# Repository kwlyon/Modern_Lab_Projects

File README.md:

# Modern Lab Projects

This repository collects four laboratory data-acquisition projects. The active
differential Arduino firmware is maintained in `Frank_Herz` and also used by
`SerialPlotter_V3`.

| Project | Contents |
| --- | --- |
| [Frank_Herz](Frank_Herz/README.md) | Franck–Hertz acquisition software and differential Arduino shield firmware |
| [SerialPlotter](SerialPlotter/README.md) | Original serial plotter and earlier shield designs |
| [SerialPlotter_V2](SerialPlotter_V2/README.md) | Two-channel recorder with the older single-ended Arduino sketch |
| [SerialPlotter_V3](SerialPlotter_V3/README.md) | General recorder, Eagle design for the current differential shield, and Arduino averaging |

The three original projects were imported with unsquashed Git subtree merges.
Their commits remain in this repository's history. Frank_Herz release tags are retained
under `Frank_Herz/v...` names so they remain distinct from future tags for other
projects.

See each project's README for build, calibration, and hardware instructions.
For the current differential shield, use the
[Frank–Herz sketch](Frank_Herz/arduino/Frank_Herz_DAQ/Frank_Herz_DAQ.ino)
with either the Frank–Herz app or Serial Plotter V3.
Frank–Hertz Windows downloads and firmware attachments are available on the
[releases page](https://github.com/kwlyon/Modern_Lab_Projects/releases).

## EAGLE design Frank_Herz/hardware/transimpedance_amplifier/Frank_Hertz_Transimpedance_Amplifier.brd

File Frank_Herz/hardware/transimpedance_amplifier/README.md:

# Frank–Hertz transimpedance amplifier

This is the separate current-to-voltage amplifier for the Frank–Hertz
experiment, **not** the Arduino acquisition shield. The original Eagle project
was `Box/eShop/Eagle/Eagle Projects/Modern Lab/Frank_Hertz`.

- [`Frank_Hertz_Transimpedance_Amplifier.sch`](Frank_Hertz_Transimpedance_Amplifier.sch) — Eagle schematic.
- [`Frank_Hertz_Transimpedance_Amplifier.brd`](Frank_Hertz_Transimpedance_Amplifier.brd) — Eagle board.
The Eagle schematic and board were copied byte for byte; only their filenames
changed. Fabrication outputs remain in the original Eagle project. Run ERC/DRC
and generate fresh Gerbers from this board before ordering boards.

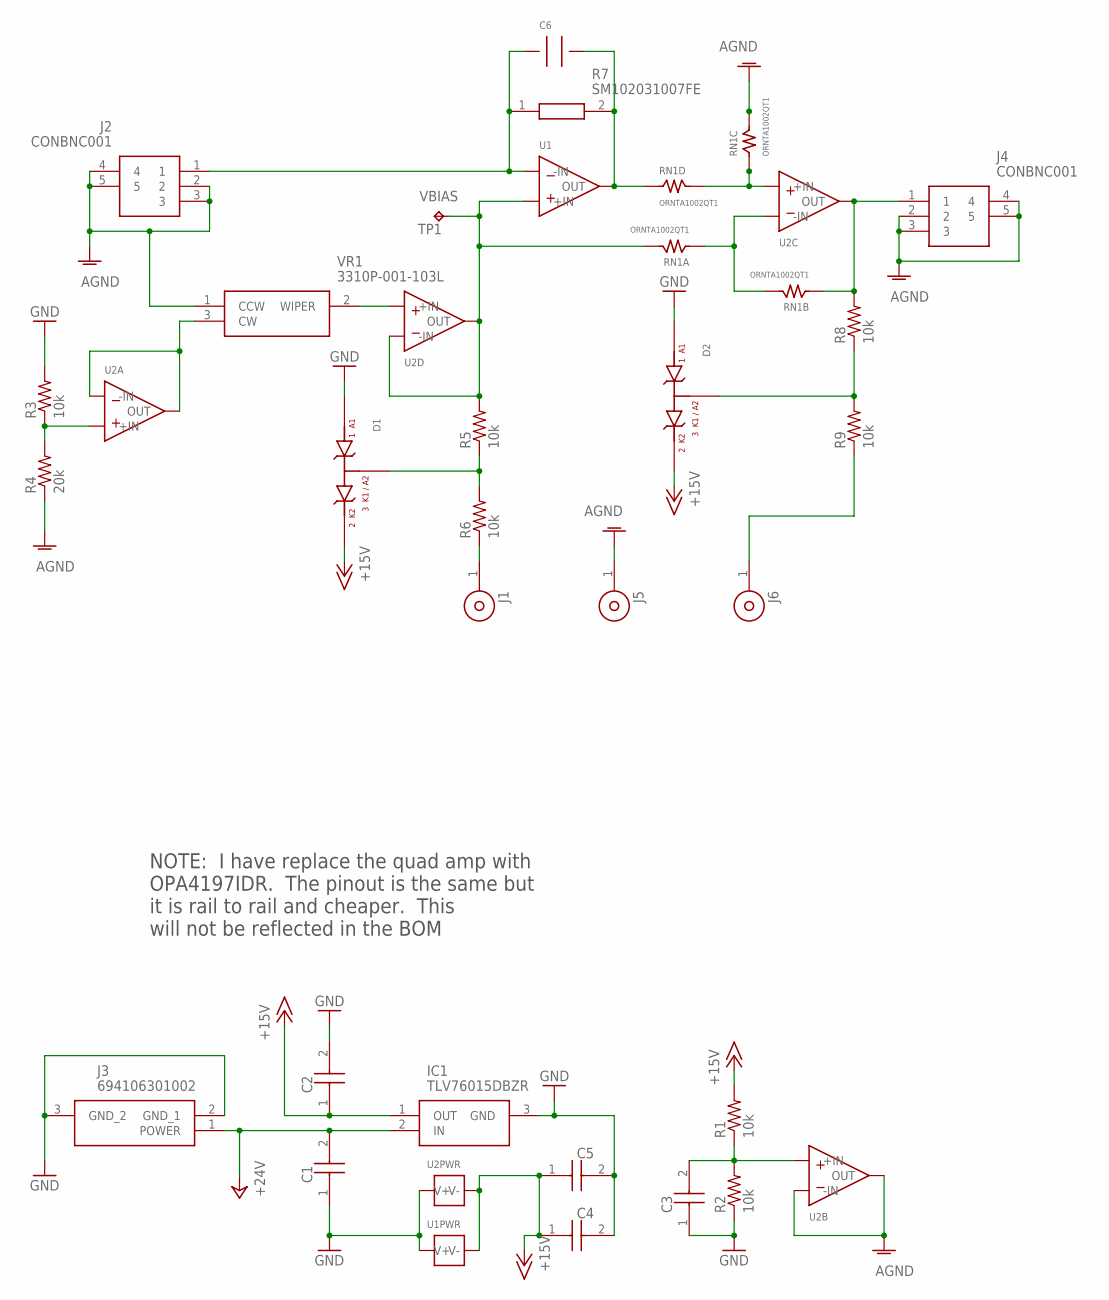
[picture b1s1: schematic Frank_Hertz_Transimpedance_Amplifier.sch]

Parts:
C1, C2, C3: 1uF; CAPC2012X140N
C4, C5: CC0603KRX7R8BB104; CAPC1608X90N
C6: C315C109D2G5TA_10.16MM; C315_BENT_10.16MM
D1, D2: BAS70_04_SOT23COMMERCIAL_REELNXP; SOT23-3_NEXPERIA
IC1: TLV76015DBZR; SOT95P237X112-3N
J1, J5, J6: CINCH_108-0904-001; CINCH_108-0904-001_BODGE
J2, J4: CONBNC001
J3: 694106301002
R1, R2, R3, R5, R6, R8, R9: 10k; R0805
R4: 20k; R0805
R7: SM102031007FE
RN1: ORNTA1002QT1; SOIC8_MS012_AA_1.27MM
TP1: TPB1,27; B1,27
U1: LMC6081IN/NOPB; PDIP-8_300MIL
U2: OPA4227UA_SOIC14; SOIC-14_D
VR1: 3310P-001-103L; 3310P001103L

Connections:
+15V: C2.1, C4.1, C5.1, D1.2 (K2), D2.2 (K2), IC1.1 (OUT), R1.2, U1.7 (V+), U2.4 (V+)
+24V: C1.2, IC1.2 (IN), J3.1 (POWER)
AGND: J2.2, J2.3, J2.4, J2.5, J4.2, J4.3, J4.4, J4.5, J5.1, R4.1, RN1.6 (2), U2.6 (-IN), U2.7 (OUT), VR1.1 (CCW)
GND: C1.1, C2.2, C3.1, C4.2, C5.2, D1.1 (A1), D2.1 (A1), IC1.3 (GND), J3.2 (GND_1), J3.3 (GND_2), R2.1, R3.2, U1.4 (V-), U2.11 (V-)
unnamed: U2.12 (+IN), VR1.2 (WIPER)
unnamed: C3.2, R1.1, R2.2, U2.5 (+IN)
unnamed: J6.1, R9.1
unnamed: R3.1, R4.2, U2.3 (+IN)
unnamed: U2.1 (OUT), U2.2 (-IN), VR1.3 (CW)
unnamed: C6.1, J2.1, R7.1, U1.2 (-IN)
unnamed: RN1.1, RN1.7 (2), U2.9 (-IN)
unnamed: C6.2, R7.2, RN1.4 (1), U1.6 (OUT)
unnamed: RN1.3 (1), RN1.5 (2), U2.10 (+IN)
unnamed: J4.1, R8.2, RN1.2 (1), U2.8 (OUT)
unnamed: D1.3 (K1_A2), R5.1, R6.2
unnamed: J1.1, R6.1
unnamed: D2.3 (K1_A2), R8.1, R9.2
VBIAS: R5.2, RN1.8 (2), TP1.TP, U1.3 (+IN), U2.13 (-IN), U2.14 (OUT)

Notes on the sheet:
NOTE: I have replace the quad amp with OPA4197IDR. The pinout is the same but it is rail to rail and cheaper. This will not be reflected in the BOM

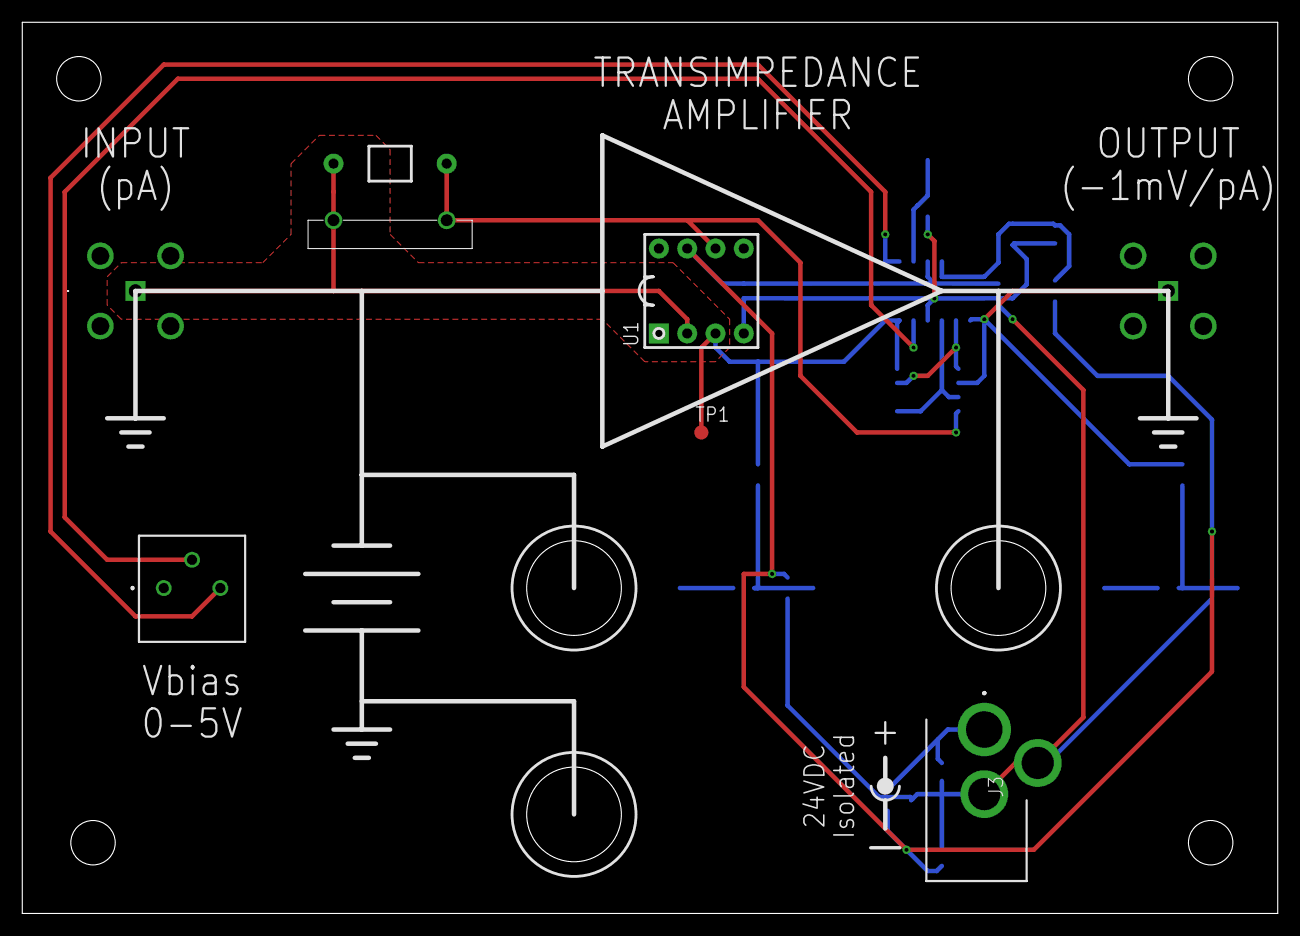
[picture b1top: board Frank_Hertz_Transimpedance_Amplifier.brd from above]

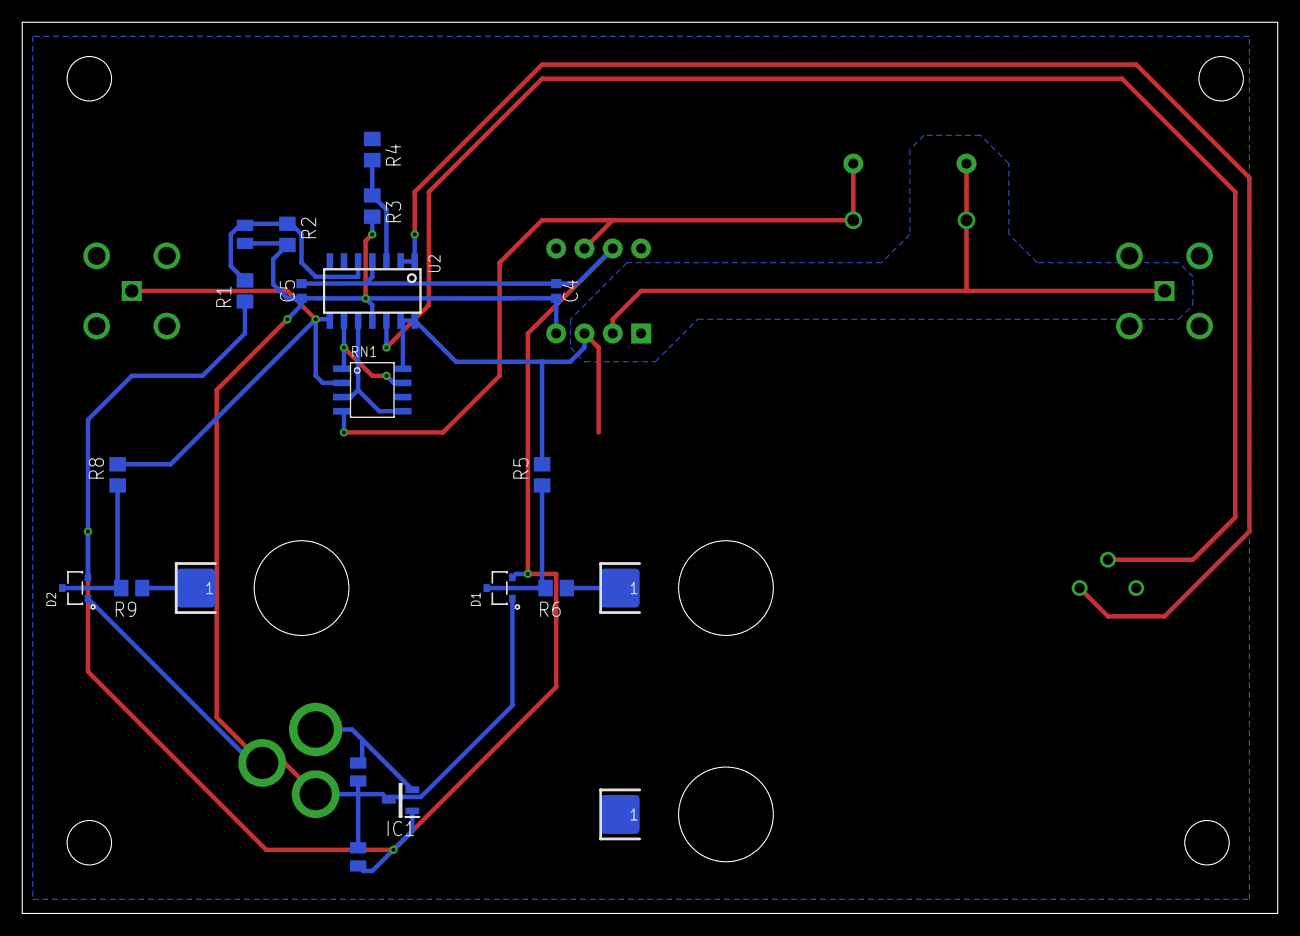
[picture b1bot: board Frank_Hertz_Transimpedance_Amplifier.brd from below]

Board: 2 copper layers, 112.7 x 80.0 mm, 29 parts (18 on the bottom side), 18 nets.

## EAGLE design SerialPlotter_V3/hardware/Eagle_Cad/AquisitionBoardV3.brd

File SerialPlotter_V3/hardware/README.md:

# Current differential Arduino shield

[`Eagle_Cad/AquisitionBoardV3.sch`](Eagle_Cad/AquisitionBoardV3.sch) and
[`Eagle_Cad/AquisitionBoardV3.brd`](Eagle_Cad/AquisitionBoardV3.brd) are the
schematic and board for the current Modern Lab shield. They were copied from
the Modern Lab **Atomic and Molecular / Arduino Shield for Aquisition** Eagle
project. Their original Eagle filenames are retained.

[`Eagle_Cad/AquisitionBoardV3_Gerbers.zip`](Eagle_Cad/AquisitionBoardV3_Gerbers.zip)
contains the corresponding fabrication outputs. The archive was copied from
that project's `CAMOutputs/GerberFiles/AquisitionV3.zip` and renamed to match
the board and schematic. Its Gerber job identifies project `AquisitionBoardV3`
and includes copper, solder mask, solder paste, silkscreen, board profile, and
drill files. The original archive remains in the Eagle project.

[`Mouser_BOM_Differential_Arduino_Shield_One_Board.xlsx`](Mouser_BOM_Differential_Arduino_Shield_One_Board.xlsx)
is a one-board parts list based on this board's placed elements. It uses the
columns from the supplied Mouser template, with added designators, footprints,
selection notes, and product links. The 21 order lines cover 56 individual
parts or kits, including one Arduino R3 stacking-header kit. The Arduino and
fabricated PCB are not included. SJ1/SJ2 are solder jumper pads and TP1 is a
bare test pad, so they do not need purchased parts. The optional AGND/BGND
header posts are listed. Check the J2 DE-9 connector's physical fit against
the Eagle footprint before ordering; its manufacturer part number is a
candidate selection. Prices and availability should be refreshed in Mouser.

The board's top silkscreen has circled **A** and **B** labels. Unlike the older
files with the same names in
[`../../SerialPlotter/Arduino Shield for Aquisition/Eagle_Cad/`](../../SerialPlotter/Arduino%20Shield%20for%20Aquisition/Eagle_Cad/),
this board has no 15-turn Bourns 3006P trimmer. The older Eagle designs stay
there for reference. Eagle may retain unused library definitions in the files;
the placed board elements are the check for whether a part is fitted.

The schematic routes Channel A through J1 and the 909 kΩ / 101 kΩ divider to
ADS1115 AIN0−AIN1. Channel B uses J3 and the corresponding divider on
AIN2−AIN3. A 10 kΩ resistor pulls the ADC's ADDR pin to +5 V for I2C address
`0x49` when solder jumper SJ1 is open. This matches the maintained
[`Frank_Herz_DAQ.ino`](../../Frank_Herz/arduino/Frank_Herz_DAQ/Frank_Herz_DAQ.ino)
firmware used by both Franck–Hertz and Serial Plotter V3.

The files were checked for matching placed parts and schematic pin connections.
Physical electrical verification and an Eagle ERC/DRC run are still needed
before fabrication or hardware changes.

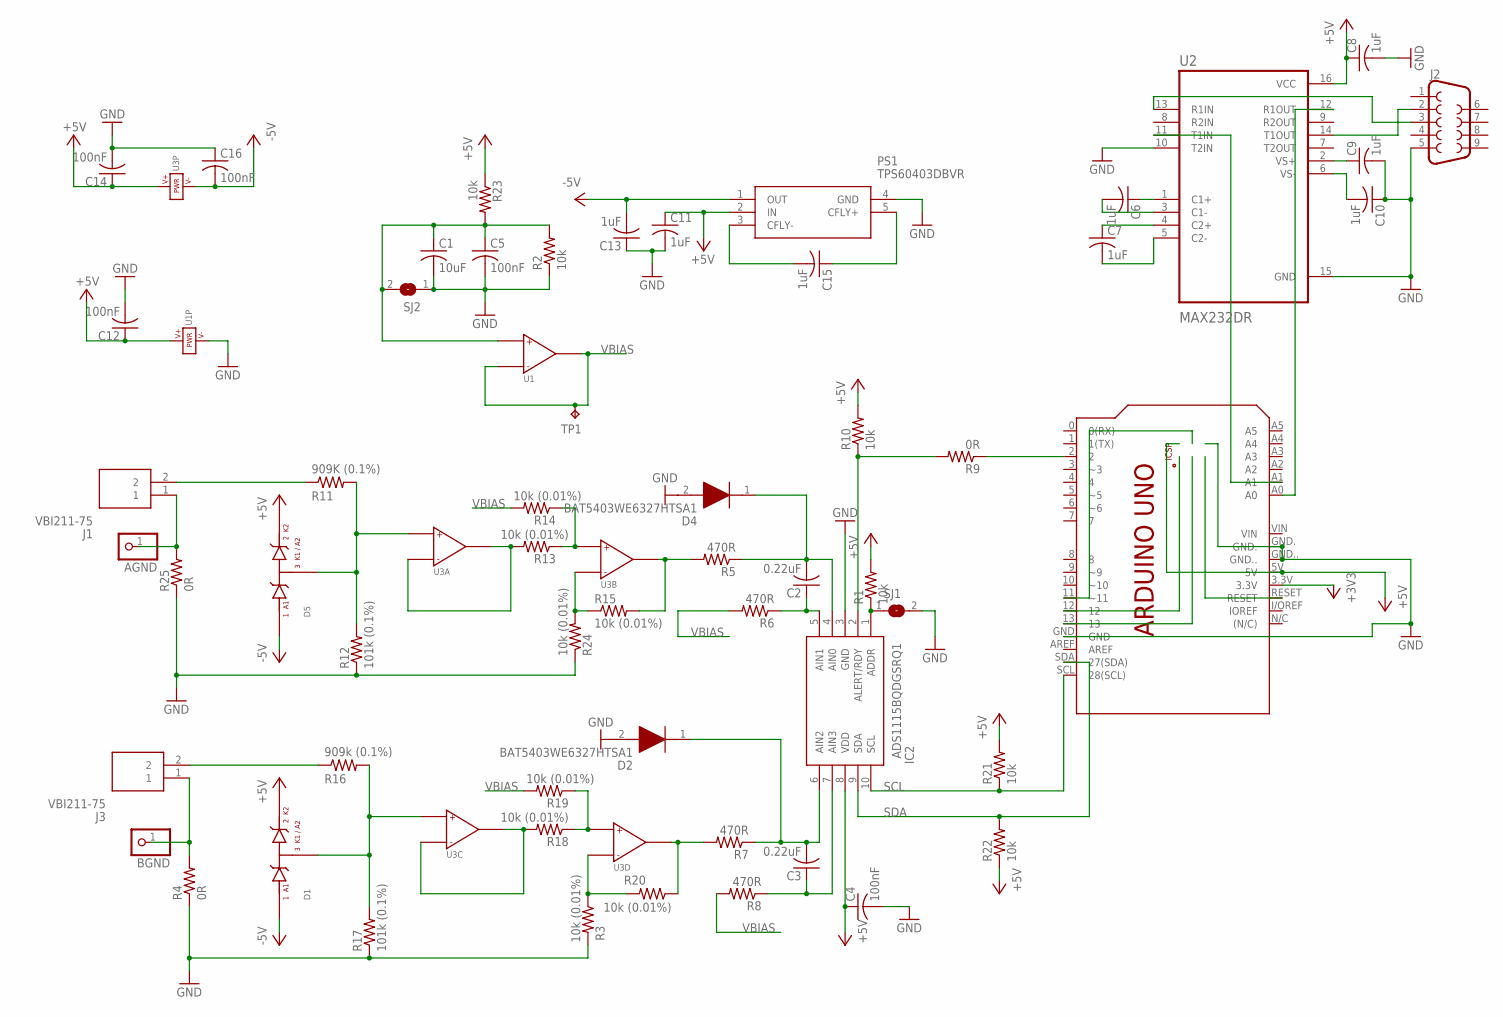
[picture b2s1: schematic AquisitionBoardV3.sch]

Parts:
AGND: PINHD-1X1; 1X01
BGND: PINHD-1X1; 1X01
C1: 10uF; C0603
C2, C3: 0.22uF; C0603
C4, C5, C12, C14, C16: 100nF; C0603
C6, C7, C8, C9, C10, C11, C13, C15: 1uF; C0603
D1, D5: BAS70_04_SOT23COMMERCIAL_REELNXP; SOT23-3_NEXPERIA
D2, D4: BAT5403WE6327HTSA1; SOD2513X110N
IC2: ADS1115BQDGSRQ1; SOP50P490X110-10N
J1, J3: VBI211-75; VBI21175
J2: DB9MALE; DB9_MALE
PCB1: ARDUINO_UNO
PS1: TPS60403DBVR; SOT95P280X145-5N
R1, R2, R10, R21, R22, R23: 10k; R0805
R3, R13, R14, R15, R18, R19, R20, R24: 10k (0.01%); R0805
R4, R9, R25: 0R; R0805
R5, R6, R7, R8: 470R; R0805
R11: 909K (0.1%); R0805
R12, R17: 101k (0.1%); R0805
R16: 909k (0.1%); R0805
SJ1, SJ2: SJ
TP1: TPB1,27; B1,27
U1: LMV321ARIDBV; TI-DBV0005A-SOT23-5
U2: MAX232DR; SOIC127P600X175-16N
U3: OPA4192; SOIC14

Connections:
+3V3: PCB1.3.3V
+5V: C4.1, C8.1, C11.1, C12.1, C14.1, D1.2 (K2), D5.2 (K2), IC2.8 (VDD), PCB1.5V, PCB1.+5V, PS1.2 (IN), R1.2, R10.2, R21.2, R22.1, R23.1, U1.5 (V+), U2.16 (VCC), U3.4 (V+)
-5V: C13.2, C16.2, D1.1 (A1), D5.1 (A1), PS1.1 (OUT), U3.11 (V-)
GND: C1.2, C4.2, C5.2, C8.2, C9.2, C10.1, C11.2, C12.2, C13.1, C14.2, C16.1, D2.2 (A), D4.2 (A), IC2.3 (GND), J2.5, PCB1.GND, PCB1.GND., PCB1.GND.., PCB1.GND_, PS1.4 (GND), R2.1, R3.2, R4.1, R12.1, R17.1, R24.1, R25.1, SJ1.2, SJ2.1, U1.2 (V-), U2.10 (T2IN), U2.15 (GND)
unnamed: J1.2, R11.1
unnamed: R13.1, R14.1, U3.5 (+IN)
unnamed: R15.1, R24.2, U3.6 (-IN)
unnamed: PCB1.RESET, PCB1.RESET.
unnamed: PCB1.13, PCB1.SCK
unnamed: R5.2, R15.2, U3.7 (OUT)
unnamed: BGND.1, J3.1, R4.2
unnamed: R7.2, R20.1, U3.14 (OUT)
unnamed: IC2.1 (ADDR), R1.1, SJ1.1
unnamed: C1.1, C5.1, R2.2, R23.2, SJ2.2, U1.3 (+IN)
unnamed: R3.1, R20.2, U3.13 (-IN)
unnamed: D5.3 (K1_A2), R11.2, R12.2, U3.3 (+IN)
unnamed: AGND.1, J1.1, R25.2
unnamed: D1.3 (K1_A2), R16.2, R17.2, U3.10 (+IN)
unnamed: C2.2, D4.1 (K), IC2.4 (AIN0), R5.1
unnamed: PCB1.12, PCB1.MISO
unnamed: PCB1.11 (~11), PCB1.MOSI
unnamed: C2.1, IC2.5 (AIN1), R6.1
unnamed: C3.2, D2.1 (K), IC2.6 (AIN2), R7.1
unnamed: J2.3, U2.13 (R1IN)
unnamed: R13.2, U3.1 (OUT), U3.2 (-IN)
unnamed: C3.1, IC2.7 (AIN3), R8.1
unnamed: IC2.2 (ALERT/RDY), R9.2, R10.1
unnamed: PCB1.2, R9.1
unnamed: J2.2, U2.14 (T1OUT)
unnamed: J3.2, R16.1
unnamed: C15.2, PS1.3 (CFLY-)
unnamed: C15.1, PS1.5 (CFLY+)
unnamed: C6.1, U2.1 (C1+)
unnamed: C6.2, U2.3 (C1-)
unnamed: C7.1, U2.4 (C2+)
unnamed: C7.2, U2.5 (C2-)
unnamed: C9.1, U2.2 (VS+)
unnamed: C10.2, U2.6 (VS-)
unnamed: R18.2, U3.8 (OUT), U3.9 (-IN)
unnamed: R18.1, R19.1, U3.12 (+IN)
unnamed: PCB1.A0, U2.12 (R1OUT)
unnamed: PCB1.A1, U2.11 (T1IN)
SCL: IC2.10 (SCL), PCB1.SCL (28(SCL)), R21.1
SDA: IC2.9 (SDA), PCB1.SDA (27(SDA)), R22.2
VBIAS: R6.2, R8.2, R14.2, R19.2, TP1.TP, U1.1 (OUT), U1.4 (-IN)

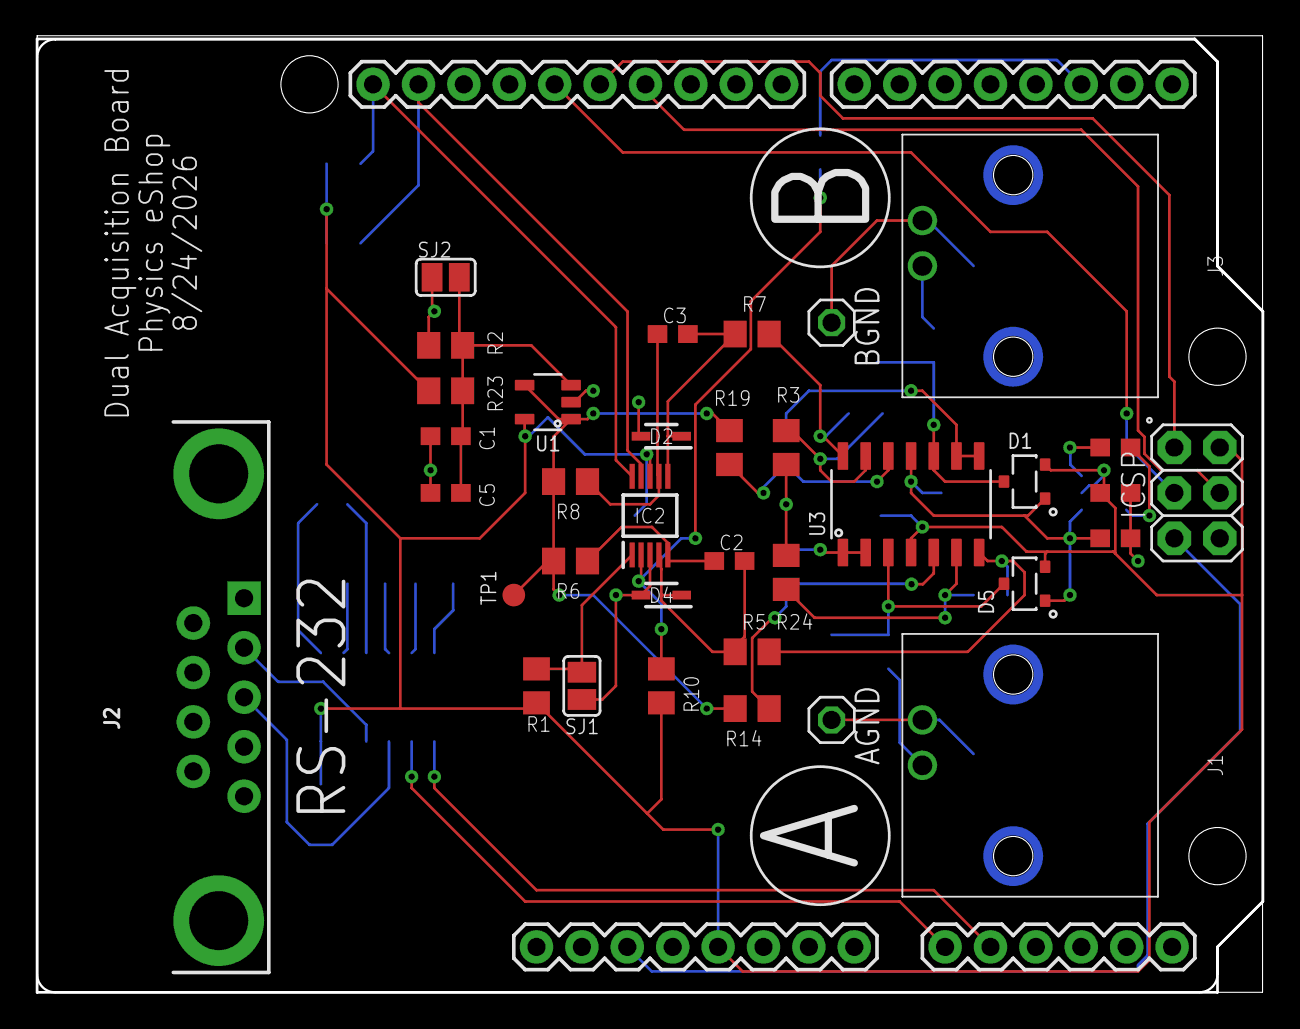
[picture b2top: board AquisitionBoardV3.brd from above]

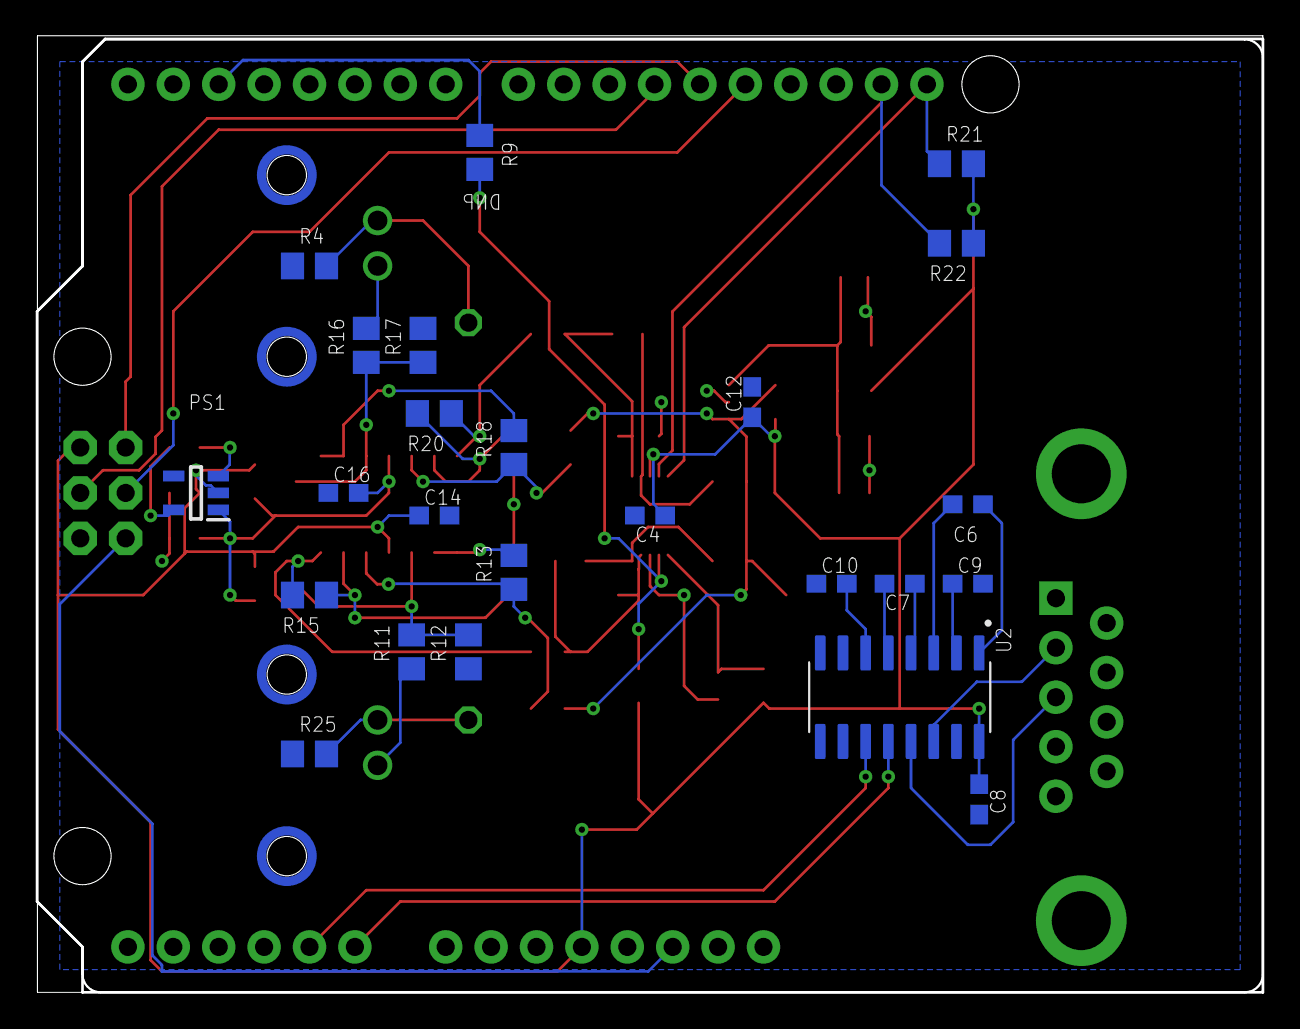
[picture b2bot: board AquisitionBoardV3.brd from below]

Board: 2 copper layers, 68.6 x 53.5 mm, 59 parts (24 on the bottom side), 44 nets.

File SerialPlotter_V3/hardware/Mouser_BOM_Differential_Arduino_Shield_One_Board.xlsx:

Mfr Part Number (Input) | Manufacturer Part Number | Mouser Part Number | Manufacturer Name | Description | Quantity 1 | Unit Price 1 | Quantity 2 | Unit Price 2 | Quantity 3 | Unit Price 3 | Quantity 4 | Unit Price 4 | Quantity 5 | Unit Price 5 | Order Quantity | Order Unit Price | Min./Mult. | Availability | Lead Time in Days | Lifecycle | NCNR | RoHS | Pb Free | Package Type | Datasheet URL | Product Image | Design Risk | Reference Designators | Eagle Footprint | Selection Note | Mouser Product URL
VBI211-75 | VBI211-75 | 530-VBI211-75 | Cinch Connectivity Solutions | 75 ohm right-angle BNC jack | 2 |  |  |  |  |  |  |  |  |  | 2 |  |  |  |  |  |  |  |  | VBI21175 |  |  |  | J1,J3 | VBI21175 |  | https://www.mouser.com/en/ProductDetail/Vitelec-Cinch-Connec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
5747250-4 | 5747250-4 | 571-5747250-4 | TE Connectivity | DE-9 male right-angle through-hole connector | 1 |  |  |  |  |  |  |  |  |  | 1 |  |  |  |  |  |  |  |  | DB9_MALE |  |  |  | J2 | DB9_MALE | Candidate standard .318-inch footprint; check mounting holes, offset, and shell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 | https://www.mouser.com/en/ProductDetail/TE-Connectivity/5747250-4
MAX232DR | MAX232DR | 595-MAX232DR | Texas Instruments | RS-232 transceiver, SOIC-16 | 1 |  |  |  |  |  |  |  |  |  | 1 |  |  |  |  |  |  |  |  | SOIC127P600X175-16N |  |  |  | U2 | SOIC127P600X175-16N |  | https://www.mouser.com/en/ProductDetail/Texas-Instruments/MAX232DR
C1608X7R1A105K080AC | C1608X7R1A105K080AC |  | TDK | 1 uF 10 V X7R 0603 ceramic capacitor | 8 |  |  |  |  |  |  |  |  |  | 8 |  |  |  |  |  |  |  |  | C0603 |  |  |  | C6,C7,C8,C9,C10,C11,C13,C15 | C0603 |  | https://www.mouser.com/en/ProductDetail/TDK/C1608X7R1A105K080AC
GCM188R71E104KA57D | GCM188R71E104KA57D |  | Murata | 100 nF 25 V X7R 0603 ceramic capacitor | 5 |  |  |  |  |  |  |  |  |  | 5 |  |  |  |  |  |  |  |  | C0603 |  |  |  | C4,C5,C12,C14,C16 | C0603 |  | https://www.mouser.com/en/ProductDetail/Murata-Electronics/G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
ADS1115BQDGSRQ1 | ADS1115BQDGSRQ1 | 595-ADS1115BQDGSRQ1 | Texas Instruments | 16-bit I2C ADC, VSSOP-10 | 1 |  |  |  |  |  |  |  |  |  | 1 |  |  |  |  |  |  |  |  | SOP50P490X110-10N |  |  |  | IC2 | SOP50P490X110-10N |  | https://www.mouser.com/en/ProductDetail/Texas-Instruments/AD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
RN73C2A909KBTDF | RN73C2A909KBTDF | 279-RN73C2A909KBTDF | TE Connectivity | 909 kohm 0.1% thin-film 0805 resistor | 2 |  |  |  |  |  |  |  |  |  | 2 |  |  |  |  |  |  |  |  | R0805 |  |  |  | R11,R16 | R0805 |  | https://gr.mouser.com/en/ProductDetail/TE-Connectivity-Holsw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
RT0805BRE07101KL | RT0805BRE07101KL |  | YAGEO | 101 kohm 0.1% thin-film 0805 resistor | 2 |  |  |  |  |  |  |  |  |  | 2 |  |  |  |  |  |  |  |  | R0805 |  |  |  | R12,R17 | R0805
RNCF0805TKW10K0 | RNCF0805TKW10K0 | 708-RNCF0805TKW10K0 | SEI Stackpole | 10 kohm 0.01% precision 0805 resistor | 8 |  |  |  |  |  |  |  |  |  | 8 |  |  |  |  |  |  |  |  | R0805 |  |  |  | R3,R13,R14,R15,R18,R19,R20,R24 | R0805 |  | https://www.mouser.com/en/ProductDetail/SEI-Stackpole/RNCF08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
RC0805FR-0710KL | RC0805FR-0710KL | 603-RC0805FR-0710KL | YAGEO | 10 kohm 1% 0805 resistor | 6 |  |  |  |  |  |  |  |  |  | 6 |  |  |  |  |  |  |  |  | R0805 |  |  |  | R1,R2,R10,R21,R22,R23 | R0805 |  | https://www.mouser.com/en/ProductDetail/YAGEO/RC0805FR-0710KL
RC0805JR-070RL | RC0805JR-070RL | 603-RC0805JR-070RL | YAGEO | 0 ohm 0805 jumper resistor | 3 |  |  |  |  |  |  |  |  |  | 3 |  |  |  |  |  |  |  |  | R0805 |  |  |  | R4,R9,R25 | R0805 |  | https://eu.mouser.com/en/ProductDetail/YAGEO/RC0805JR-070RL
GRM188R61A106ME69D | GRM188R61A106ME69D |  | Murata | 10 uF 10 V X5R 0603 ceramic capacitor | 1 |  |  |  |  |  |  |  |  |  | 1 |  |  |  |  |  |  |  |  | C0603 |  |  |  | C1 | C0603 | Check effective capacitance at 5 V bias before assembly. | https://eu.mouser.com/en/ProductDetail/Murata-Electronics/GR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
LMV321AIDBVR | LMV321AIDBVR | 595-LMV321AIDBVR | Texas Instruments | Single op amp, SOT-23-5 | 1 |  |  |  |  |  |  |  |  |  | 1 |  |  |  |  |  |  |  |  | TI-DBV0005A-SOT23-5 |  |  |  | U1 | TI-DBV0005A-SOT23-5 |  | https://www.mouser.com/en/ProductDetail/Texas-Instruments/LM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
BAS70-04-QR | BAS70-04-QR | 771-BAS70-04-QR | Nexperia | Dual-series Schottky diode, SOT-23-3 | 2 |  |  |  |  |  |  |  |  |  | 2 |  |  |  |  |  |  |  |  | SOT23-3_NEXPERIA |  |  |  | D1,D5 | SOT23-3_NEXPERIA | Available BAS70-04 SOT-23 ordering variant. | https://www.mouser.com/en/ProductDetail/Nexperia/BAS70-04-QR
OPA4192ID | OPA4192ID | 595-OPA4192ID | Texas Instruments | Quad precision op amp, SOIC-14 | 1 |  |  |  |  |  |  |  |  |  | 1 |  |  |  |  |  |  |  |  | SOIC14 |  |  |  | U3 | SOIC14 |  | https://www.mouser.com/en/ProductDetail/Texas-Instruments/OPA4192ID
RC0805FR-07470RL | RC0805FR-07470RL |  | YAGEO | 470 ohm 1% 0805 resistor | 4 |  |  |  |  |  |  |  |  |  | 4 |  |  |  |  |  |  |  |  | R0805 |  |  |  | R5,R6,R7,R8 | R0805 |  | https://br.mouser.com/ProductDetail/YAGEO/RC0805FR-07470RL
GRM188R71C224KA01J | GRM188R71C224KA01J |  | Murata | 0.22 uF 16 V X7R 0603 ceramic capacitor | 2 |  |  |  |  |  |  |  |  |  | 2 |  |  |  |  |  |  |  |  | C0603 |  |  |  | C2,C3 | C0603 |  | https://www.mouser.com/en/ProductDetail/Murata-Electronics/G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
TPS60403DBVRG4 | TPS60403DBVRG4 | 595-TPS60403DBVRG4 | Texas Instruments | 60 mA charge-pump inverter, SOT-23-5 | 1 |  |  |  |  |  |  |  |  |  | 1 |  |  |  |  |  |  |  |  | SOT95P280X145-5N |  |  |  | PS1 | SOT95P280X145-5N | DBVRG4 is the RoHS ordering variant of schematic value TPS60403DBVR. | https://www.mouser.com/en/ProductDetail/Texas-Instruments/TP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
BAT5403WE6327HTSA1 | BAT5403WE6327HTSA1 | 726-BAT5403WE6327HTS | Infineon | Schottky diode, SOD-323 | 2 |  |  |  |  |  |  |  |  |  | 2 |  |  |  |  |  |  |  |  | SOD2513X110N |  |  |  | D2,D4 | SOD2513X110N |  | https://www.mouser.com/en/ProductDetail/Infineon-Technologie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
929400-01-01-RK | 929400-01-01-RK | 517-929400-01-01-RK | 3M | 1-pin straight through-hole ground header | 2 |  |  |  |  |  |  |  |  |  | 2 |  |  |  |  |  |  |  |  | 1X01 |  |  |  | AGND,BGND | 1X01 | Optional ground posts; may be omitted if wires are soldered directly. | https://www.mouser.com/ProductDetail/3M-Electronic-Solutions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
85 | 85 | 485-85 | Adafruit | Arduino R3 shield stacking-header kit | 1 |  |  |  |  |  |  |  |  |  | 1 |  |  |  |  |  |  |  |  | ARDUINO_UNO |  |  |  | PCB1 | ARDUINO_UNO | Kit includes 1x10, 2x8, 2x6 and 2x3 headers; one 1x6 is extra. Arduino and PCB 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 | https://www.mouser.com/en/ProductDetail/Adafruit/85

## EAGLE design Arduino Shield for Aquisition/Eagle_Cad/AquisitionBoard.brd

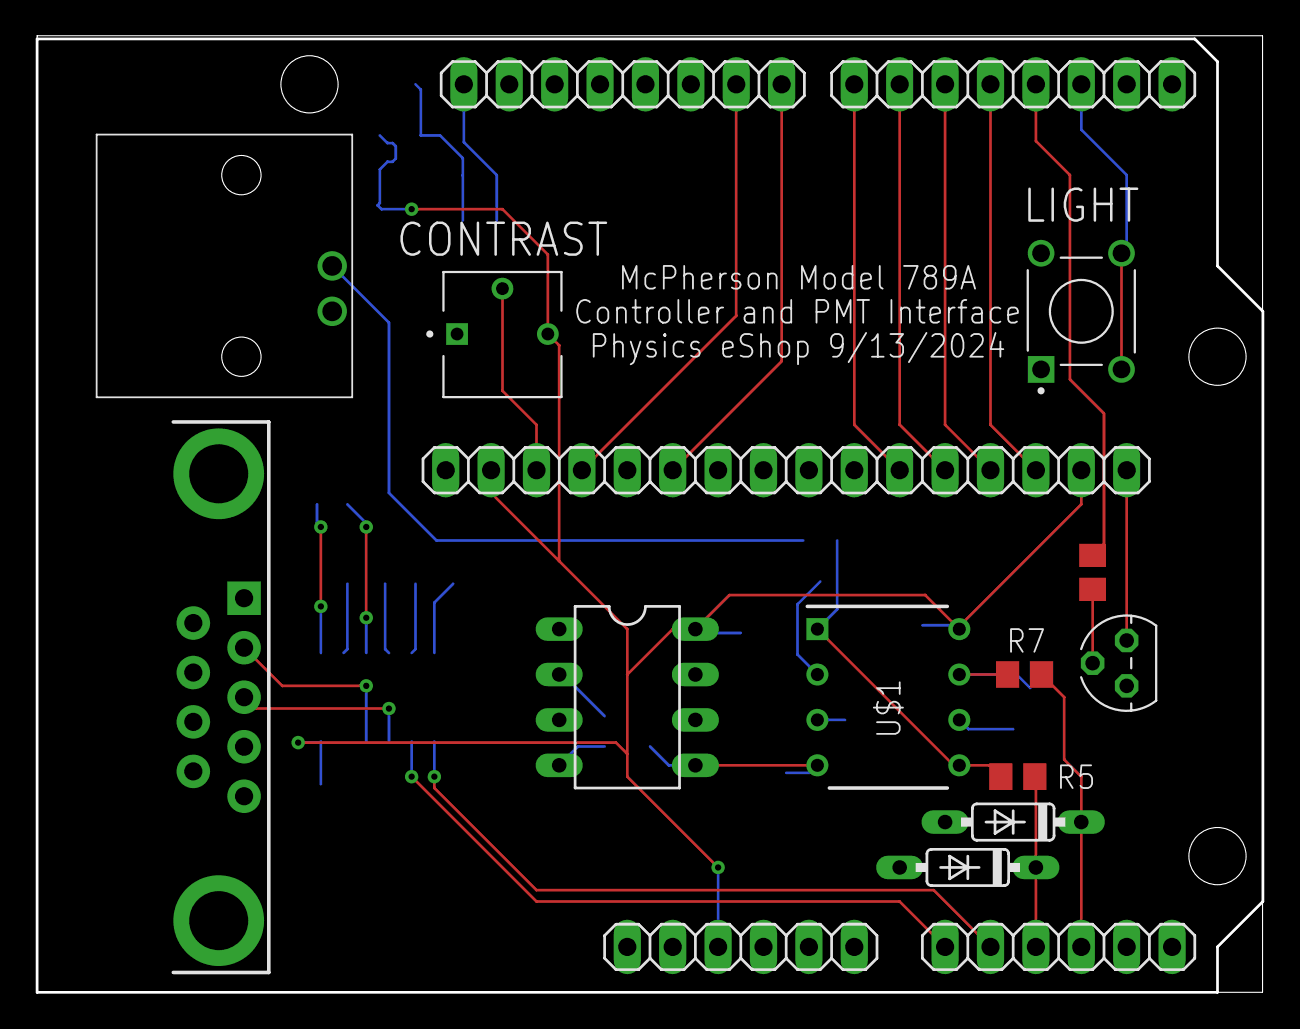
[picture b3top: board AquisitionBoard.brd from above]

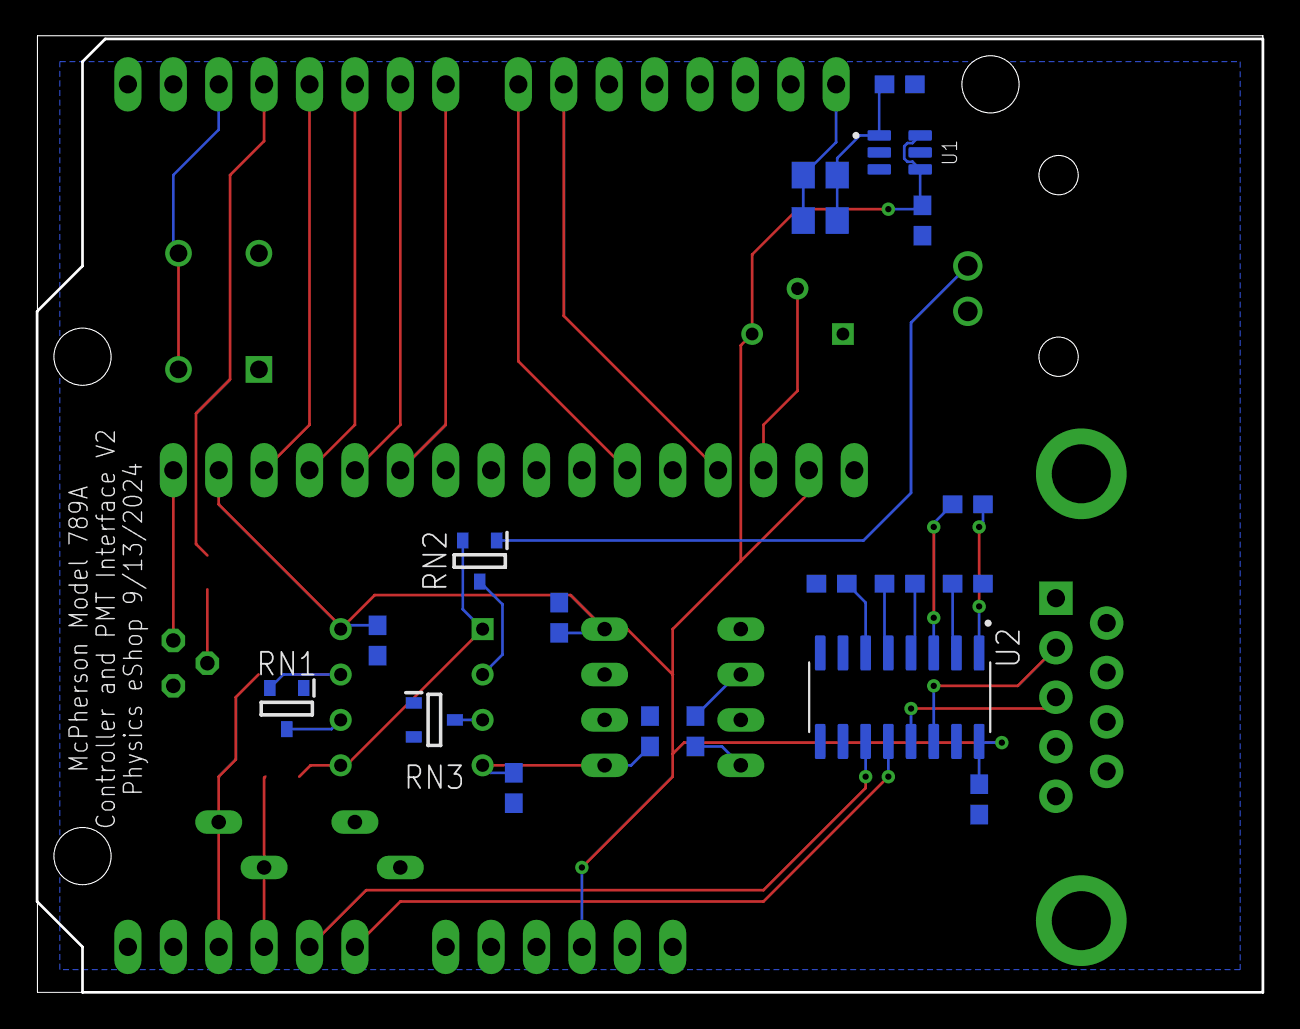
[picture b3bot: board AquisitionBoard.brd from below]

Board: 2 copper layers, 68.6 x 53.5 mm, 33 parts (19 on the bottom side), 36 nets.

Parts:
C1, C2, C3: 10uF; C0603
C4, C6, C7, C8, C9, C10: 1uF; C0603
C5, C11, C12: 1nF; C0603
D1, D2: 1N4148DO35-7; DO35-7
IC1: ARDUINO2009_2
IC3: ICL7660CPA; DIL08
J1: VBI211-75; VBI21175
J2: DB9_MALE
JP1: 1X16
R4, R9: 10k; R0805
R5, R7, R8: 240R; R0805
RN1: MPMT10019001AT1; SOT95P230X102-3N
RN2, RN3: MPMT2001AT1; SOT95P230X102-3N
SW1: 1825910-6; SW_1825910-6-4
T1: 2N3904; TO92
U1: MCP1501T-18E/CHY; SOT95P280X145-6N
U2: MAX232DR; SOIC127P600X175-16N
U$1: OPA2227MOD; DIP794W53P254L959H508Q8N
VR1: 3362P-1-103LF; TRIM_3362P-1-103LF

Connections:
+5V: C3.1, C4.1, C8.1, C12.1, IC1.3, IC3.8, JP1.2, JP1.15, U1.4, U1.6, U2.16, U$1.8, VR1.3
-5V: C2.1, C11.2, IC3.5, U$1.4
GND: C2.2, C3.2, C4.2, C5.2, C8.2, C9.2, C10.1, C11.1, C12.2, D1.A, D2.A, IC1.4, IC1.5, IC1.27, IC3.3, IC3.6, J1.1, J2.5, JP1.1, JP1.5, JP1.7, JP1.8, JP1.9, JP1.10, RN1.1, RN3.1, RN3.2, SW1.1, SW1.2, T1.3, U1.2, U1.3, U1.5, U2.15, VR1.1
unnamed: J1.2, RN2.1
unnamed: C1.1, IC3.2
unnamed: C1.2, IC3.4
unnamed: IC1.16, R8.1
unnamed: R7.2, RN1.2, U$1.7
unnamed: R5.2, RN2.2, U$1.1, U$1.5
unnamed: D1.C, IC1.9, R5.1
unnamed: IC1.28, R4.2, R9.2
unnamed: D2.C, IC1.10, R7.1
unnamed: RN2.3, U$1.2
unnamed: IC1.8, U2.11
unnamed: IC1.7, U2.12
unnamed: RN1.3, U$1.6
unnamed: RN3.3, U$1.3
unnamed: JP1.3, VR1.2
unnamed: IC1.17, JP1.14
unnamed: IC1.18, JP1.13
unnamed: J2.3, U2.13
unnamed: IC1.19, JP1.12
unnamed: C5.1, R4.1, R9.1, U1.1
unnamed: JP1.16, T1.1
unnamed: IC1.20, JP1.11
unnamed: J2.2, U2.14
unnamed: IC1.22, JP1.4
unnamed: IC1.15, SW1.3, SW1.4
unnamed: R8.2, T1.2
unnamed: C6.1, U2.1
unnamed: C6.2, U2.3
unnamed: C7.1, U2.4
unnamed: C7.2, U2.5
unnamed: C9.1, U2.2
unnamed: C10.2, U2.6
unnamed: IC1.21, JP1.6

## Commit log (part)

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2026-06-16 Initial SerialPlotter repository

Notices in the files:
parts and their libraries:
SparkFun-Connectors: Licensing: Creative Commons ShareAlike 4.0 International - https://creativecommons.org/licenses/by-sa/4.0
